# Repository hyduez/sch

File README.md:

# A Super Cool Hub

This project implements a budget and cool USB Hub thanks to the OTG USB feature that ESP32 S2/S3 brings on! On [BOM.md](https://github.com/hyduez/sch/blob/master/BOM.md) u can find each component with its own link to Aliexpress/Mouser. Due to expensive carriers fees and the niche market of Ecuador, it could be more than 20$ USD. The only firmware u are gonna need, is based on the brain of this PCB; if u want to do something when a state is detected, change the switch to flash the ESP32 and start coding. Anyways, this project aimed to be more; include OLED displays with tact buttons and commands to toggle data traveling, power on ports and show stats on the displays.

Here is the schematic:

You can see a lot of stuff that maybe u dont know where to start. But, as always, start where the power arises. Focus on the CH334F, it's the Mini Hub with 4 ports and another one for the host to manage, in this case, ESP32 S3 WROOM. It provides almost all the energy on the PCB, we are interesed on the 5V-A net label; it's gonna be merged with another line, 5V-B from SparkFun DEV-14050 (based on CH340G), this last one serve as auxiliar line, if u need more power available. Merged, they produce 5V-C, who is in charge of the USBs VBUS and ESP32 S3 WROOM power.

> [!IMPORTANT]
> Notice that this schematic is working with an ESP32 S3 WROOM, that's the reason why there's an AMS1117-3.3 that decrease the voltage from 5V to 3.3V; that's not neccesary with ESP32 S3 Devkit, since it brings its own regulator.

> [!TIP]
> Machine-readable fabrication outputs (Gerbers, drill, BOM CSV, pick and place,
> DRC/ERC) live in [`fabrication/`](fabrication), along with a
> [parts cross-check](fabrication/parts-check.md) against the BOM below. Before
> ordering, note that the PCB uses the bare CH334F QFN-24 and the bare
> ESP32-S3-WROOM-1 module, not the Adafruit breakout / devkit listed in
> [`BOM.md`](BOM.md).

The idea is that u'd add another coproccesor and create an useful artcraft hardware made by your hands, something to be proud. It's cool. You're not flexing something u bought on a minimarket, it's something u built and that's what matters.

## Index

- Inspiration & References
- Data Sheets & Components
- PCB Design
- Fabrication Files

## Inspiration & References
This is my first Hardware project strictly speaking. Instead of following guides, tutorials, projects pre-made; I decided to try it on my own. And here is how I got it: first, u need theory. It migh sounds cliche, but it's neccesary; u cannot start a journey without knowning how to start. Second, u must put into practice, and expand upon, what you DON'T KNOW; u might understand the fundamentals, but u cannot stop there, u've to be willing to try new and unfamiliar things. It seems too hard to make it? That doesn't matter, u're way ahead of it and u MUST be.

I started the last week without knowning even what a SMD, THT or SMT was, but that wasn't excuse to try in 2 days something REALLY cool, while managing a presencial event. I've already a sort of ideas that I wanted to do these 10 weeks, but I'm gonna stay to the most approachable and tuff thing to do. Between a lot of references, I've taken notice of this [resource](https://www.cnx-software.com/2024/11/04/usb-insight-hub-open-source-esp32-s2-based-for-testing-usb-devices/); and this image was an amazing motivation to design and build it.

## Data Sheets & Components

| Part | What it's for | Qty | Unit | Total | Vendor |
| --- | --- | --- | --- | --- | --- |
| [ESP32-S3 Devkit](https://es.aliexpress.com/item/1005008752956562.html?spm=a2g0o.productlist.main.2.56ea6619hSHeNG&algo_pvid=a7dce044-b750-4d39-8121-3cc3f7c3f446&algo_exp_id=a7dce044-b750-4d39-8121-3cc3f7c3f446-1&pdp_ext_f=%7B%22order%22%3A%224094%22%2C%22spu_best_type%22%3A%22price%22%2C%22eval%22%3A%221%22%2C%22fromPage%22%3A%22search%22%7D&pdp_npi=6%40dis%21USD%212.70%212.38%21%21%212.70%212.38%21%402141137e17917628397458067e0f4a%2112000048852579349%21sea%21EC%210%21ABX%211%210%21n_tag%3A-29910%3Bd%3A12ba086b%3Bm03_new_user%3A-29895&curPageLogUid=cDxGKN6VLdgP&utparam-url=scene%3Asearch%7Cquery_from%3A%7Cx_object_id%3A1005008752956562%7C_p_origin_prod%3A) | USB OTG and logic (more uses with the displays) | 1 | $2.38 | $2.38 | [Aliexpress](https://es.aliexpress.com/item/1005008752956562.html?spm=a2g0o.productlist.main.2.56ea6619hSHeNG&algo_pvid=a7dce044-b750-4d39-8121-3cc3f7c3f446&algo_exp_id=a7dce044-b750-4d39-8121-3cc3f7c3f446-1&pdp_ext_f=%7B%22order%22%3A%224094%22%2C%22spu_best_type%22%3A%22price%22%2C%22eval%22%3A%221%22%2C%22fromPage%22%3A%22search%22%7D&pdp_npi=6%40dis%21USD%212.70%212.38%21%21%212.70%212.38%21%402141137e17917628397458067e0f4a%2112000048852579349%21sea%21EC%210%21ABX%211%210%21n_tag%3A-29910%3Bd%3A12ba086b%3Bm03_new_user%3A-29895&curPageLogUid=cDxGKN6VLdgP&utparam-url=scene%3Asearch%7Cquery_from%3A%7Cx_object_id%3A1005008752956562%7C_p_origin_prod%3A) |
| [Adafruit CH334F 5999 Mini Hub USB 4 Ports](https://es.aliexpress.com/item/1005012286577528.html?spm=a2g0o.productlist.main.2.14c930fdv5VAiO&algo_pvid=f13fedb9-842e-44d2-a92c-3b4c332d380f&algo_exp_id=f13fedb9-842e-44d2-a92c-3b4c332d380f-1&pdp_ext_f=%7B%22order%22%3A%2260%22%2C%22spu_best_type%22%3A%22price%22%2C%22eval%22%3A%221%22%2C%22fromPage%22%3A%22search%22%7D&pdp_npi=6%40dis%21USD%214.55%214.55%21%21%2130.30%2130.30%21%400b08c0c217917628955407391e0cc5%2112000057968741991%21sea%21EC%210%21ABX%211%210%21n_tag%3A-29910%3Bd%3A12ba086b%3Bm03_new_user%3A-29895&curPageLogUid=nbacit8oiS5x&utparam-url=scene%3Asearch%7Cquery_from%3A%7Cx_object_id%3A1005012286577528%7C_p_origin_prod%3A) | USB Host and other ports, provides 5V to them | 1 | $4.55 | $4.55 | [Aliexpress](https://es.aliexpress.com/item/1005012286577528.html?spm=a2g0o.productlist.main.2.14c930fdv5VAiO&algo_pvid=f13fedb9-842e-44d2-a92c-3b4c332d380f&algo_exp_id=f13fedb9-842e-44d2-a92c-3b4c332d380f-1&pdp_ext_f=%7B%22order%22%3A%2260%22%2C%22spu_best_type%22%3A%22price%22%2C%22eval%22%3A%221%22%2C%22fromPage%22%3A%22search%22%7D&pdp_npi=6%40dis%21USD%214.55%214.55%21%21%2130.30%2130.30%21%400b08c0c217917628955407391e0cc5%2112000057968741991%21sea%21EC%210%21ABX%211%210%21n_tag%3A-29910%3Bd%3A12ba086b%3Bm03_new_user%3A-29895&curPageLogUid=nbacit8oiS5x&utparam-url=scene%3Asearch%7Cquery_from%3A%7Cx_object_id%3A1005012286577528%7C_p_origin_prod%3A) |
| [AMS1117-3.3](https://es.aliexpress.com/item/1005011789112180.html?spm=a2g0o.productlist.main.8.1d7940d1IDOKxH&algo_pvid=8ebd24b2-7b8b-4a43-9fbc-c8b7aa6dfdef&algo_exp_id=8ebd24b2-7b8b-4a43-9fbc-c8b7aa6dfdef-7&pdp_ext_f=%7B%22order%22%3A%22255%22%2C%22eval%22%3A%221%22%2C%22fromPage%22%3A%22search%22%7D&pdp_npi=6%40dis%21USD%214.50%212.07%21%21%2129.96%2113.78%21%402140cf5017917629953643864e0c9e%2112000056560577594%21sea%21EC%210%21ABX%211%210%21n_tag%3A-29910%3Bd%3A12ba086b%3Bm03_new_user%3A-29895&curPageLogUid=DT8fVeHC2Z0u&utparam-url=scene%3Asearch%7Cquery_from%3A%7Cx_object_id%3A1005011789112180%7C_p_origin_prod%3A) | Convert 5V to 3.3V (it shouldn't be neccesary because devkit editions use to bring their own regulators) | 1 | $2.07 | $2.07 | [Aliexpress](https://es.aliexpress.com/item/1005011789112180.html?spm=a2g0o.productlist.main.8.1d7940d1IDOKxH&algo_pvid=8ebd24b2-7b8b-4a43-9fbc-c8b7aa6dfdef&algo_exp_id=8ebd24b2-7b8b-4a43-9fbc-c8b7aa6dfdef-7&pdp_ext_f=%7B%22order%22%3A%22255%22%2C%22eval%22%3A%221%22%2C%22fromPage%22%3A%22search%22%7D&pdp_npi=6%40dis%21USD%214.50%212.07%21%21%2129.96%2113.78%21%402140cf5017917629953643864e0c9e%2112000056560577594%21sea%21EC%210%21ABX%211%210%21n_tag%3A-29910%3Bd%3A12ba086b%3Bm03_new_user%3A-29895&curPageLogUid=DT8fVeHC2Z0u&utparam-url=scene%3Asearch%7Cquery_from%3A%7Cx_object_id%3A1005011789112180%7C_p_origin_prod%3A) |
| [Resistors (10k)](https://es.aliexpress.com/item/1005012752130462.html?spm=a2g0o.productlist.main.17.1c8b2c1aXSGf5r&algo_pvid=4282fd54-1a4b-4560-b2d5-20b68522da93&algo_exp_id=4282fd54-1a4b-4560-b2d5-20b68522da93-16&pdp_ext_f=%7B%22order%22%3A%22129%22%2C%22eval%22%3A%221%22%2C%22fromPage%22%3A%22search%22%7D&pdp_npi=6%40dis%21USD%210.85%210.78%21%21%210.85%210.78%21%402140cf5017917630669585191e0c9e%2112000059788474300%21sea%21EC%210%21ABX%211%210%21n_tag%3A-29910%3Bd%3A12ba086b%3Bm03_new_user%3A-29895&curPageLogUid=QCaruf2H9BXq&utparam-url=scene%3Asearch%7Cquery_from%3A%7Cx_object_id%3A1005012752130462%7C_p_origin_prod%3A) | Electronics | 1 | $0.78 | $0.78 | [Aliexpress](https://es.aliexpress.com/item/1005012752130462.html?spm=a2g0o.productlist.main.17.1c8b2c1aXSGf5r&algo_pvid=4282fd54-1a4b-4560-b2d5-20b68522da93&algo_exp_id=4282fd54-1a4b-4560-b2d5-20b68522da93-16&pdp_ext_f=%7B%22order%22%3A%22129%22%2C%22eval%22%3A%221%22%2C%22fromPage%22%3A%22search%22%7D&pdp_npi=6%40dis%21USD%210.85%210.78%21%21%210.85%210.78%21%402140cf5017917630669585191e0c9e%2112000059788474300%21sea%21EC%210%21ABX%211%210%21n_tag%3A-29910%3Bd%3A12ba086b%3Bm03_new_user%3A-29895&curPageLogUid=QCaruf2H9BXq&utparam-url=scene%3Asearch%7Cquery_from%3A%7Cx_object_id%3A1005012752130462%7C_p_origin_prod%3A) |
| [Capacitor (1uf)](https://es.aliexpress.com/item/1005003382101471.html?spm=a2g0o.productlist.main.3.617723cbL9pqqJ&algo_pvid=187cdbcc-065d-4fdd-bee1-079ebf859f36&algo_exp_id=187cdbcc-065d-4fdd-bee1-079ebf859f36-2&pdp_ext_f=%7B%22order%22%3A%22134%22%2C%22eval%22%3A%221%22%2C%22fromPage%22%3A%22search%22%7D&pdp_npi=6%40dis%21USD%210.83%210.82%21%21%215.50%215.44%21%40210159d417917631330304275e0d23%2112000025520782166%21sea%21EC%210%21ABX%211%210%21n_tag%3A-29910%3Bd%3A12ba086b%3Bm03_new_user%3A-29895&curPageLogUid=pA2ZzqVH0y7b&utparam-url=scene%3Asearch%7Cquery_from%3A%7Cx_object_id%3A1005003382101471%7C_p_origin_prod%3A) | Electronics | 1 | $0.82 | $0.82 | [Aliexpress](https://es.aliexpress.com/item/1005003382101471.html?spm=a2g0o.productlist.main.3.617723cbL9pqqJ&algo_pvid=187cdbcc-065d-4fdd-bee1-079ebf859f36&algo_exp_id=187cdbcc-065d-4fdd-bee1-079ebf859f36-2&pdp_ext_f=%7B%22order%22%3A%22134%22%2C%22eval%22%3A%221%22%2C%22fromPage%22%3A%22search%22%7D&pdp_npi=6%40dis%21USD%210.83%210.82%21%21%215.50%215.44%21%40210159d417917631330304275e0d23%2112000025520782166%21sea%21EC%210%21ABX%211%210%21n_tag%3A-29910%3Bd%3A12ba086b%3Bm03_new_user%3A-29895&curPageLogUid=pA2ZzqVH0y7b&utparam-url=scene%3Asearch%7Cquery_from%3A%7Cx_object_id%3A1005003382101471%7C_p_origin_prod%3A) |
| [Capacitor (10uf)](https://es.aliexpress.com/item/1005004338780216.html?spm=a2g0o.productlist.main.3.322223e9fjoMPA&algo_pvid=524ed1cf-a28f-4dc1-a7a2-89a9e72d1312&algo_exp_id=524ed1cf-a28f-4dc1-a7a2-89a9e72d1312-2&pdp_ext_f=%7B%22order%22%3A%22237%22%2C%22eval%22%3A%221%22%2C%22fromPage%22%3A%22search%22%7D&pdp_npi=6%40dis%21USD%210.97%210.68%21%21%210.97%210.68%21%40212e37e817917631883788663e0c8f%2112000028814428355%21sea%21EC%210%21ABX%211%210%21n_tag%3A-29910%3Bd%3A12ba086b%3Bm03_new_user%3A-29895&curPageLogUid=EJPw3F4KWMpT&utparam-url=scene%3Asearch%7Cquery_from%3A%7Cx_object_id%3A1005004338780216%7C_p_origin_prod%3A) | Electronics | 1 | $0.68 | $0.68 | [Aliexpress](https://es.aliexpress.com/item/1005004338780216.html?spm=a2g0o.productlist.main.3.322223e9fjoMPA&algo_pvid=524ed1cf-a28f-4dc1-a7a2-89a9e72d1312&algo_exp_id=524ed1cf-a28f-4dc1-a7a2-89a9e72d1312-2&pdp_ext_f=%7B%22order%22%3A%22237%22%2C%22eval%22%3A%221%22%2C%22fromPage%22%3A%22search%22%7D&pdp_npi=6%40dis%21USD%210.97%210.68%21%21%210.97%210.68%21%40212e37e817917631883788663e0c8f%2112000028814428355%21sea%21EC%210%21ABX%211%210%21n_tag%3A-29910%3Bd%3A12ba086b%3Bm03_new_user%3A-29895&curPageLogUid=EJPw3F4KWMpT&utparam-url=scene%3Asearch%7Cquery_from%3A%7Cx_object_id%3A1005004338780216%7C_p_origin_prod%3A) |
| [Led Diode](https://es.aliexpress.com/item/1005004543292837.html?spm=a2g0o.productlist.main.1.21d0e14dVRjCgZ&algo_pvid=ccc14f9d-805c-4f90-938d-073c46266c18&algo_exp_id=ccc14f9d-805c-4f90-938d-073c46266c18-0&pdp_ext_f=%7B%22order%22%3A%226583%22%2C%22spu_best_type%22%3A%22price%22%2C%22eval%22%3A%221%22%2C%22fromPage%22%3A%22search%22%7D&pdp_npi=6%40dis%21USD%212.07%211.97%21%21%2113.76%2113.07%21%40212e37e817917633191452847e0c8f%2112000029546625285%21sea%21EC%210%21ABX%211%210%21n_tag%3A-29910%3Bd%3A12ba086b%3Bm03_new_user%3A-29895&curPageLogUid=2ixU2qk83hql&utparam-url=scene%3Asearch%7Cquery_from%3A%7Cx_object_id%3A1005004543292837%7C_p_origin_prod%3A) | Misc | 1 | $1.97 | $1.97 | [Aliexpress](https://es.aliexpress.com/item/1005004543292837.html?spm=a2g0o.productlist.main.1.21d0e14dVRjCgZ&algo_pvid=ccc14f9d-805c-4f90-938d-073c46266c18&algo_exp_id=ccc14f9d-805c-4f90-938d-073c46266c18-0&pdp_ext_f=%7B%22order%22%3A%226583%22%2C%22spu_best_type%22%3A%22price%22%2C%22eval%22%3A%221%22%2C%22fromPage%22%3A%22search%22%7D&pdp_npi=6%40dis%21USD%212.07%211.97%21%21%2113.76%2113.07%21%40212e37e817917633191452847e0c8f%2112000029546625285%21sea%21EC%210%21ABX%211%210%21n_tag%3A-29910%3Bd%3A12ba086b%3Bm03_new_user%3A-29895&curPageLogUid=2ixU2qk83hql&utparam-url=scene%3Asearch%7Cquery_from%3A%7Cx_object_id%3A1005004543292837%7C_p_origin_prod%3A) |
| [CH340G USB-C Female 3.3V & 5V](https://es.aliexpress.com/item/1005009973324450.html?spm=a2g0o.productlist.main.8.2ea226deptqf7i&algo_pvid=015248a2-db7a-48a4-b338-fae4d3fea4a1&algo_exp_id=015248a2-db7a-48a4-b338-fae4d3fea4a1-7&pdp_ext_f=%7B%22order%22%3A%22165%22%2C%22spu_best_type%22%3A%22price%22%2C%22eval%22%3A%221%22%2C%22fromPage%22%3A%22search%22%7D&pdp_npi=6%40dis%21USD%213.86%211.85%21%21%2125.72%2112.35%21%40210159a517917633550661626e0cf8%2112000050730857128%21sea%21EC%210%21ABX%211%210%21n_tag%3A-29910%3Bd%3A12ba086b%3Bm03_new_user%3A-29895&curPageLogUid=ahEIKOvfgL6V&utparam-url=scene%3Asearch%7Cquery_from%3A%7Cx_object_id%3A1005009973324450%7C_p_origin_prod%3A) | Auxiliar energy source | 1 | $1.85 | $1.85 | [Aliexpress](https://es.aliexpress.com/item/1005009973324450.html?spm=a2g0o.productlist.main.8.2ea226deptqf7i&algo_pvid=015248a2-db7a-48a4-b338-fae4d3fea4a1&algo_exp_id=015248a2-db7a-48a4-b338-fae4d3fea4a1-7&pdp_ext_f=%7B%22order%22%3A%22165%22%2C%22spu_best_type%22%3A%22price%22%2C%22eval%22%3A%221%22%2C%22fromPage%22%3A%22search%22%7D&pdp_npi=6%40dis%21USD%213.86%211.85%21%21%2125.72%2112.35%21%40210159a517917633550661626e0cf8%2112000050730857128%21sea%21EC%210%21ABX%211%210%21n_tag%3A-29910%3Bd%3A12ba086b%3Bm03_new_user%3A-29895&curPageLogUid=ahEIKOvfgL6V&utparam-url=scene%3Asearch%7Cquery_from%3A%7Cx_object_id%3A1005009973324450%7C_p_origin_prod%3A) |
| [1N5819 Diodes Schottky](https://es.aliexpress.com/item/32854878050.html?spm=a2g0o.productlist.main.1.711f4f10e92eCH&algo_pvid=0c70d40a-1a3c-4e26-88f5-180aee8b8167&algo_exp_id=0c70d40a-1a3c-4e26-88f5-180aee8b8167-0&pdp_ext_f=%7B%22order%22%3A%22114%22%2C%22eval%22%3A%221%22%2C%22fromPage%22%3A%22search%22%7D&pdp_npi=6%40dis%21USD%211.13%211.07%21%21%211.13%211.07%21%40210159a517917634506883193e0cf8%2165279246473%21sea%21EC%210%21ABX%211%210%21n_tag%3A-29910%3Bd%3A12ba086b%3Bm03_new_user%3A-29895&curPageLogUid=gfQc0vqEISYV&utparam-url=scene%3Asearch%7Cquery_from%3A%7Cx_object_id%3A32854878050%7C_p_origin_prod%3A) | Power muxer between CH334F and CH340G 5V | 1 | $1.07 | $1.07 | [Aliexpress](https://es.aliexpress.com/item/32854878050.html?spm=a2g0o.productlist.main.1.711f4f10e92eCH&algo_pvid=0c70d40a-1a3c-4e26-88f5-180aee8b8167&algo_exp_id=0c70d40a-1a3c-4e26-88f5-180aee8b8167-0&pdp_ext_f=%7B%22order%22%3A%22114%22%2C%22eval%22%3A%221%22%2C%22fromPage%22%3A%22search%22%7D&pdp_npi=6%40dis%21USD%211.13%211.07%21%21%211.13%211.07%21%40210159a517917634506883193e0cf8%2165279246473%21sea%21EC%210%21ABX%211%210%21n_tag%3A-29910%3Bd%3A12ba086b%3Bm03_new_user%3A-29895&curPageLogUid=gfQc0vqEISYV&utparam-url=scene%3Asearch%7Cquery_from%3A%7Cx_object_id%3A32854878050%7C_p_origin_prod%3A) |
| [Capacitor (100nf) (KGM05AR51A104KN)](https://www.mouser.ec/en/ProductDetail/KYOCERA-AVX/KGM05AR51A104KN?qs=Jm2GQyTW%2Fbi5bvYnwKdugg%3D%3D) | Electronics | 2 | $0.32 | $0.64 | [Mouser](https://www.mouser.ec/en/ProductDetail/KYOCERA-AVX/KGM05AR51A104KN?qs=Jm2GQyTW%2Fbi5bvYnwKdugg%3D%3D) |
| [Tactil Button 4.3](https://es.aliexpress.com/item/1005005549119220.html?spm=a2g0o.productlist.main.1.5ccd1020kha8Bg&algo_pvid=2b03a42a-50ce-4adc-afa1-d793b0f735b8&algo_exp_id=2b03a42a-50ce-4adc-afa1-d793b0f735b8-0&pdp_ext_f=%7B%22order%22%3A%22513%22%2C%22eval%22%3A%221%22%2C%22fromPage%22%3A%22search%22%7D&pdp_npi=6%40dis%21USD%210.88%210.79%21%21%210.88%210.79%21%402102f7bd17917638156187256e0fd4%2112000033497740421%21sea%21EC%210%21ABX%211%210%21n_tag%3A-29910%3Bd%3A12ba086b%3Bm03_new_user%3A-29895&curPageLogUid=2k5vIwR9Gi5m&utparam-url=scene%3Asearch%7Cquery_from%3A%7Cx_object_id%3A1005005549119220%7C_p_origin_prod%3A) | Switch for the ESP32 | 1 | $0.79 | $0.79 | [Aliexpress](https://es.aliexpress.com/item/1005005549119220.html?spm=a2g0o.productlist.main.1.5ccd1020kha8Bg&algo_pvid=2b03a42a-50ce-4adc-afa1-d793b0f735b8&algo_exp_id=2b03a42a-50ce-4adc-afa1-d793b0f735b8-0&pdp_ext_f=%7B%22order%22%3A%22513%22%2C%22eval%22%3A%221%22%2C%22fromPage%22%3A%22search%22%7D&pdp_npi=6%40dis%21USD%210.88%210.79%21%21%210.88%210.79%21%402102f7bd17917638156187256e0fd4%2112000033497740421%21sea%21EC%210%21ABX%211%210%21n_tag%3A-29910%3Bd%3A12ba086b%3Bm03_new_user%3A-29895&curPageLogUid=2k5vIwR9Gi5m&utparam-url=scene%3Asearch%7Cquery_from%3A%7Cx_object_id%3A1005005549119220%7C_p_origin_prod%3A) |
| [Hook-up Wires](https://es.aliexpress.com/item/1005008563576114.html?spm=a2g0o.productlist.main.1.664d4b4b7wJWWy&algo_pvid=39365065-7a89-4fde-bb6e-e4ea4540c1a9&algo_exp_id=39365065-7a89-4fde-bb6e-e4ea4540c1a9-0&pdp_ext_f=%7B%22order%22%3A%2231223%22%2C%22spu_best_type%22%3A%22price%22%2C%22eval%22%3A%221%22%2C%22fromPage%22%3A%22search%22%7D&pdp_npi=6%40dis%21USD%213.71%213.71%21%21%2124.70%2124.70%21%402101528c17917638773475139e0fd4%2112000045733462558%21sea%21EC%210%21ABX%211%210%21n_tag%3A-29910%3Bd%3A12ba086b%3Bm03_new_user%3A-29895&curPageLogUid=A20gy6g0xdJd&utparam-url=scene%3Asearch%7Cquery_from%3A%7Cx_object_id%3A1005008563576114%7C_p_origin_prod%3A) | To connect everything | 1 | $3.71 | $3.71 | [Aliexpress](https://es.aliexpress.com/item/1005008563576114.html?spm=a2g0o.productlist.main.1.664d4b4b7wJWWy&algo_pvid=39365065-7a89-4fde-bb6e-e4ea4540c1a9&algo_exp_id=39365065-7a89-4fde-bb6e-e4ea4540c1a9-0&pdp_ext_f=%7B%22order%22%3A%2231223%22%2C%22spu_best_type%22%3A%22price%22%2C%22eval%22%3A%221%22%2C%22fromPage%22%3A%22search%22%7D&pdp_npi=6%40dis%21USD%213.71%213.71%21%21%2124.70%2124.70%21%402101528c17917638773475139e0fd4%2112000045733462558%21sea%21EC%210%21ABX%211%210%21n_tag%3A-29910%3Bd%3A12ba086b%3Bm03_new_user%3A-29895&curPageLogUid=A20gy6g0xdJd&utparam-url=scene%3Asearch%7Cquery_from%3A%7Cx_object_id%3A1005008563576114%7C_p_origin_prod%3A) |
| [USB-A Dip Connector 2.54mm](https://es.aliexpress.com/item/1005010686097914.html?spm=a2g0o.productlist.main.32.627d120a9faCQe&algo_pvid=ec453c04-842f-4509-b627-83b8270896d8&algo_exp_id=ec453c04-842f-4509-b627-83b8270896d8-31&pdp_ext_f=%7B%22order%22%3A%2254%22%2C%22eval%22%3A%221%22%2C%22fromPage%22%3A%22search%22%7D&pdp_npi=6%40dis%21USD%212.89%212.31%21%21%2119.24%2115.39%21%402101364a17917639668701473e0e3c%2112000053188161885%21sea%21EC%210%21ABX%211%210%21n_tag%3A-29910%3Bd%3A12ba086b%3Bm03_new_user%3A-29895&curPageLogUid=wjXYxHCDXvPi&utparam-url=scene%3Asearch%7Cquery_from%3A%7Cx_object_id%3A1005010686097914%7C_p_origin_prod%3A) | That's kinda obvious. | 1 | $2.31 | $2.31 | [Aliexpress](https://es.aliexpress.com/item/1005010686097914.html?spm=a2g0o.productlist.main.32.627d120a9faCQe&algo_pvid=ec453c04-842f-4509-b627-83b8270896d8&algo_exp_id=ec453c04-842f-4509-b627-83b8270896d8-31&pdp_ext_f=%7B%22order%22%3A%2254%22%2C%22eval%22%3A%221%22%2C%22fromPage%22%3A%22search%22%7D&pdp_npi=6%40dis%21USD%212.89%212.31%21%21%2119.24%2115.39%21%402101364a17917639668701473e0e3c%2112000053188161885%21sea%21EC%210%21ABX%211%210%21n_tag%3A-29910%3Bd%3A12ba086b%3Bm03_new_user%3A-29895&curPageLogUid=wjXYxHCDXvPi&utparam-url=scene%3Asearch%7Cquery_from%3A%7Cx_object_id%3A1005010686097914%7C_p_origin_prod%3A) |
| **Parts subtotal** | — | — | — | **$23.62** | — |
| **Tax & shipping** | — | — | — | **$20.00** | — |
| **Total** | — | — | — | **$43.62** | — |

And also the following data sheets:

- [CH334F](https://cdn-learn.adafruit.com/assets/assets/000/131/435/original/CH334DS1.PDF)
- [ESP32 S3 Schematic Checklist](https://docs.espressif.com/projects/esp-hardware-design-guidelines/en/latest/esp32s3/schematic-checklist.html)

and even more, but they are missed.

## PCB Design

I have to be honest, it was kinda messy, but it was part of my learning and I'm okay with it :p I designed it more than three times in a row just to make it look prettier and logic, not only wiring for the sake of doing it. I learnt a lot of things and I'm feeling more conformtable using KiCAD (schematic, pcb desing) and I hope I'm gonna do the same with the CAD week! I'm gonna take a look to the guide of this week, I hope to see a tutorial on OpenShape.

I also hope to build this project on week 6 and bring it to live, wait some updates on it anyways on the next days/weeks/months. I'm so excited to keep learning and participating on Half Life!! :)

## Fabrication Files

Everything a fab house or an assembly service needs is generated from the KiCad
project and checked in under [`fabrication/`](fabrication):

| What | File |
| --- | --- |
| Gerbers + drill (upload this to the PCB house) | [`fabrication/sch-gerbers.zip`](fabrication/sch-gerbers.zip) |
| Plain Gerbers (X2, 9 layers) | [`fabrication/gerbers/`](fabrication/gerbers) |
| Drill files (Excellon, mm, PTH/NPTH split) + maps | [`fabrication/drill/`](fabrication/drill) |
| Bill of materials (CSV, grouped by value) | [`fabrication/bom/sch-bom.csv`](fabrication/bom/sch-bom.csv) |
| Pick and place / centroid (CSV, mm) | [`fabrication/pick-and-place/`](fabrication/pick-and-place) |
| DRC + ERC + board stats | [`fabrication/reports/`](fabrication/reports) |
| Schematic & PCB PDFs | [`fabrication/plots/`](fabrication/plots) |

The board is 2 layers, 1.6 mm, 81.1 x 75.6 mm, with 22 footprints (18 SMD, 4
THT), all placed on the front side, so it can be assembled with a single-side
stencil. [`BOM.md`](BOM.md) is the shopping list from Half Life with vendor
links; the CSV in `fabrication/bom/` is the machine-readable version generated
from the schematic, so the two are worth cross-checking before ordering.

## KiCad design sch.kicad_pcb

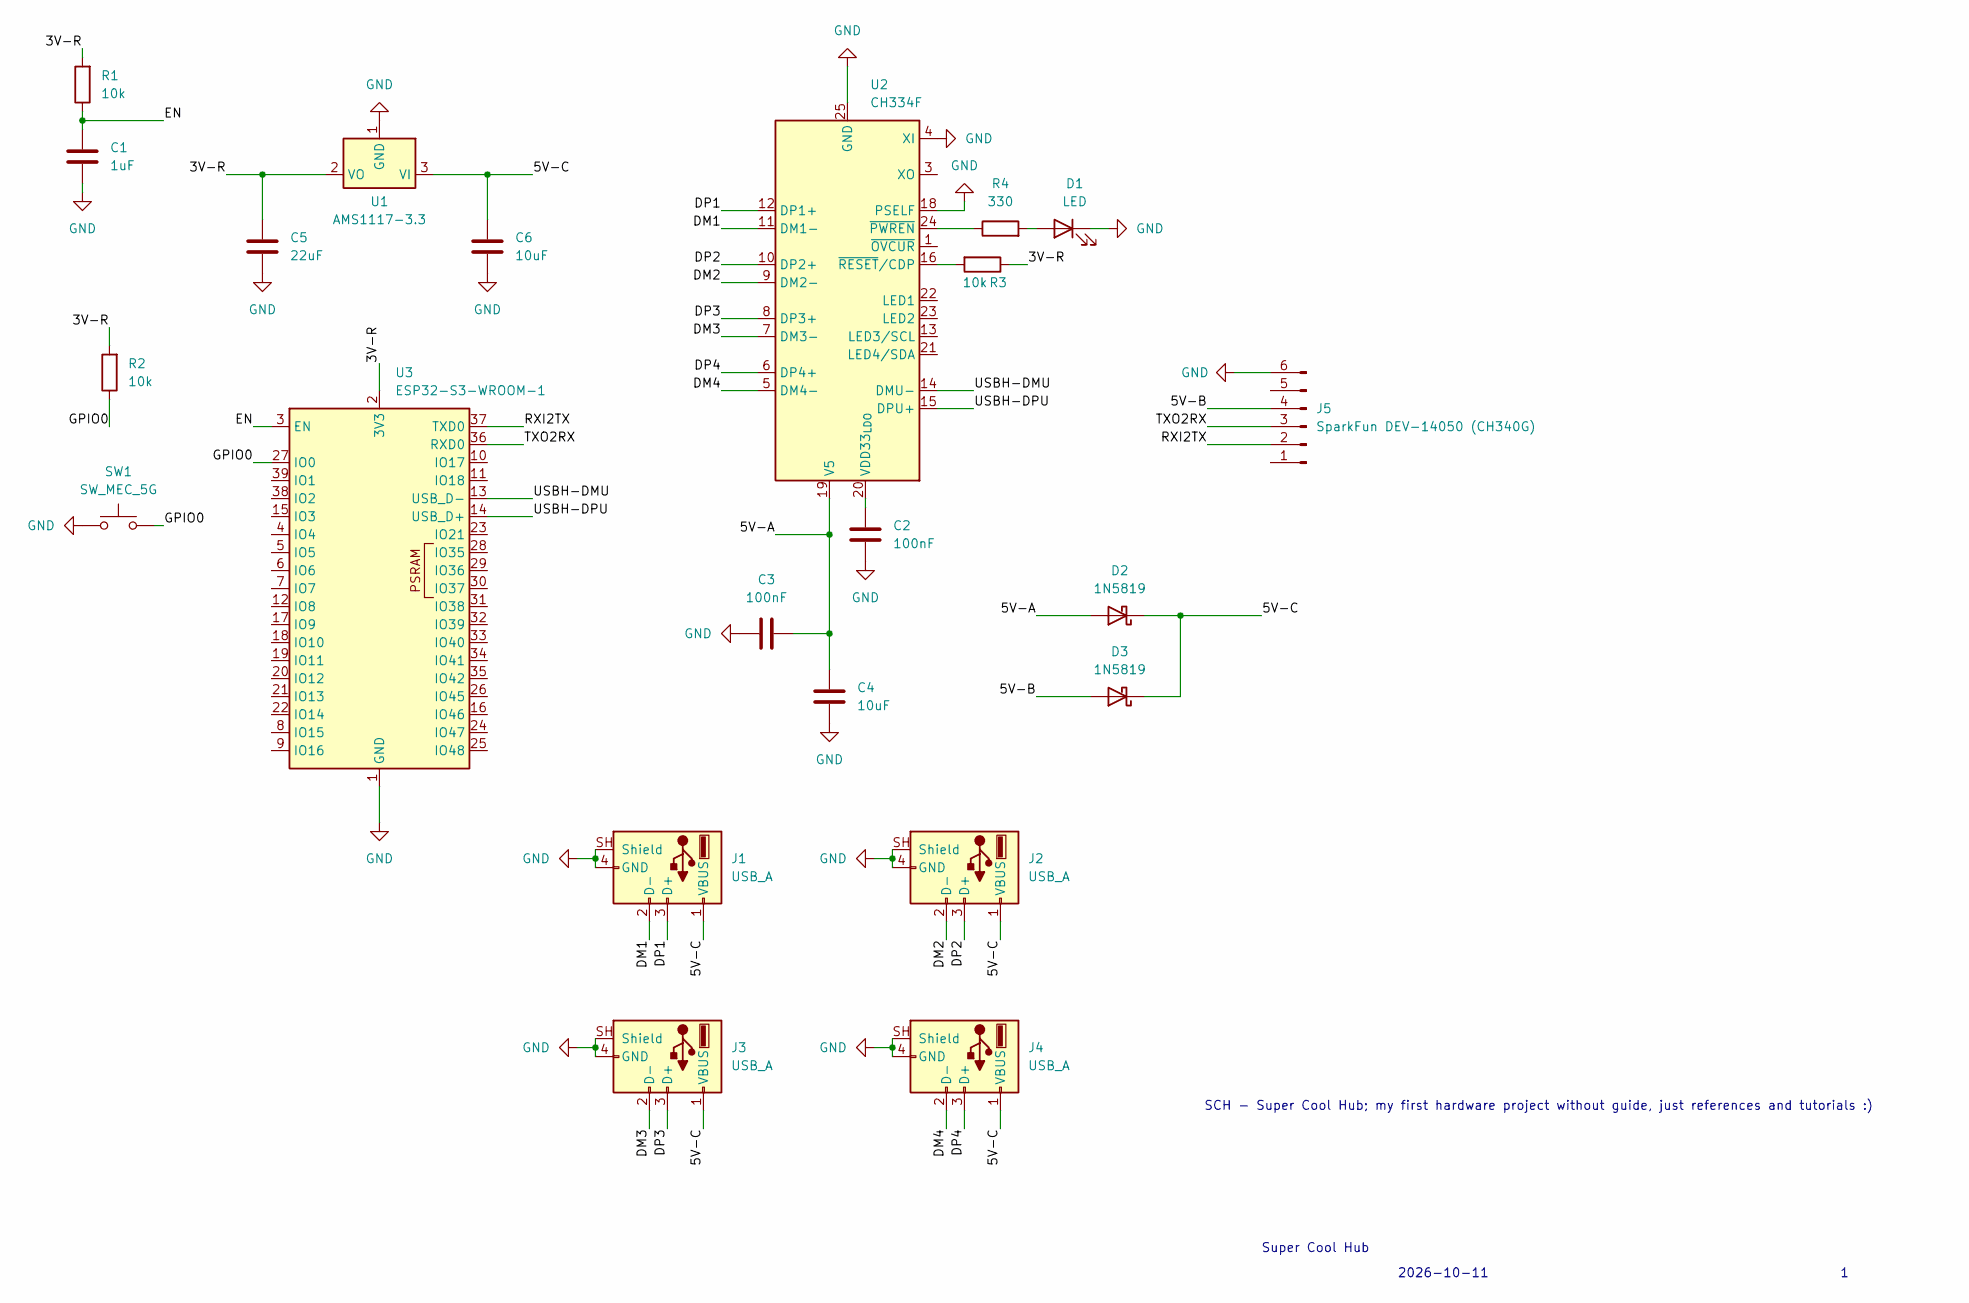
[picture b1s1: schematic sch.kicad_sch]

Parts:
C1: 1uF; C_0805_2012Metric
C2, C3: 100nF; C_0805_2012Metric
C4, C6: 10uF; C_0805_2012Metric
C5: 22uF; C_0805_2012Metric
D1: LED; LED_0805_2012Metric
D2, D3: 1N5819; D_DO-41_SOD81_P10.16mm_Horizontal
J1, J2, J3, J4: USB_A; USB_A_Connfly_DS1098_Horizontal
J5: SparkFun DEV-14050 (CH340G); PinHeader_1x06_P2.54mm_Vertical
R1, R2, R3: 10k; R_0805_2012Metric
R4: 330; R_0805_2012Metric
SW1: SW_MEC_5G; SW_PUSH_6mm
U1: AMS1117-3.3; SOT-223-3_TabPin2
U2: CH334F; QFN-24-1EP_4x4mm_P0.5mm_EP2.7x2.7mm
U3: ESP32-S3-WROOM-1

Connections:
/3V-R: C5.1, R1.2, R2.2, R3.1, U1.2 (VO), U3.2 (3V3)
/5V-A: C3.2, C4.2, D2.2 (A), U2.19 (V5)
/5V-B: D3.2 (A), J5.4
/5V-C: C6.1, D2.1 (K), D3.1 (K), J1.1 (VBUS), J2.1 (VBUS), J3.1 (VBUS), J4.1 (VBUS), U1.3 (VI)
/DM1: J1.2 (D-), U2.11 (DM1-)
/DM2: J2.2 (D-), U2.9 (DM2-)
/DM3: J3.2 (D-), U2.7 (DM3-)
/DM4: J4.2 (D-), U2.5 (DM4-)
/DP1: J1.3 (D+), U2.12 (DP1+)
/DP2: J2.3 (D+), U2.10 (DP2+)
/DP3: J3.3 (D+), U2.8 (DP3+)
/DP4: J4.3 (D+), U2.6 (DP4+)
/EN: C1.1, R1.1, U3.3 (EN)
/GPIO0: R2.1, SW1.3 (B), SW1.4 (B), U3.27 (IO0)
/RXI2TX: J5.2, U3.37 (TXD0)
/TXO2RX: J5.3, U3.36 (RXD0)
/USBH-DMU: U2.14 (DMU-), U3.13 (USB_D-)
/USBH-DPU: U2.15 (DPU+), U3.14 (USB_D+)
GND: C1.2, C2.2, C3.1, C4.1, C5.2, C6.2, D1.1 (K), J1.4 (GND), J1.SH (Shield), J2.4 (GND), J2.SH (Shield), J3.4 (GND), J3.SH (Shield), J4.4 (GND), J4.SH (Shield), J5.6, SW1.1 (A), SW1.2 (A), U1.1 (GND), U2.4 (XI), U2.18 (PSELF), U2.25 (GND), U3.1 (GND), U3.40 (GND), U3.41 (GND)
unnamed: D1.2 (A), R4.2
unnamed: C2.1, U2.20 (VDD33_{LDO})
unnamed: R4.1, U2.24 (~PWREN)
unnamed: R3.2, U2.16 (~RESET/CDP)

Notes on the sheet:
2026-10-11
SCH - Super Cool Hub; my first hardware project without guide, just references and tutorials :)
Super Cool Hub

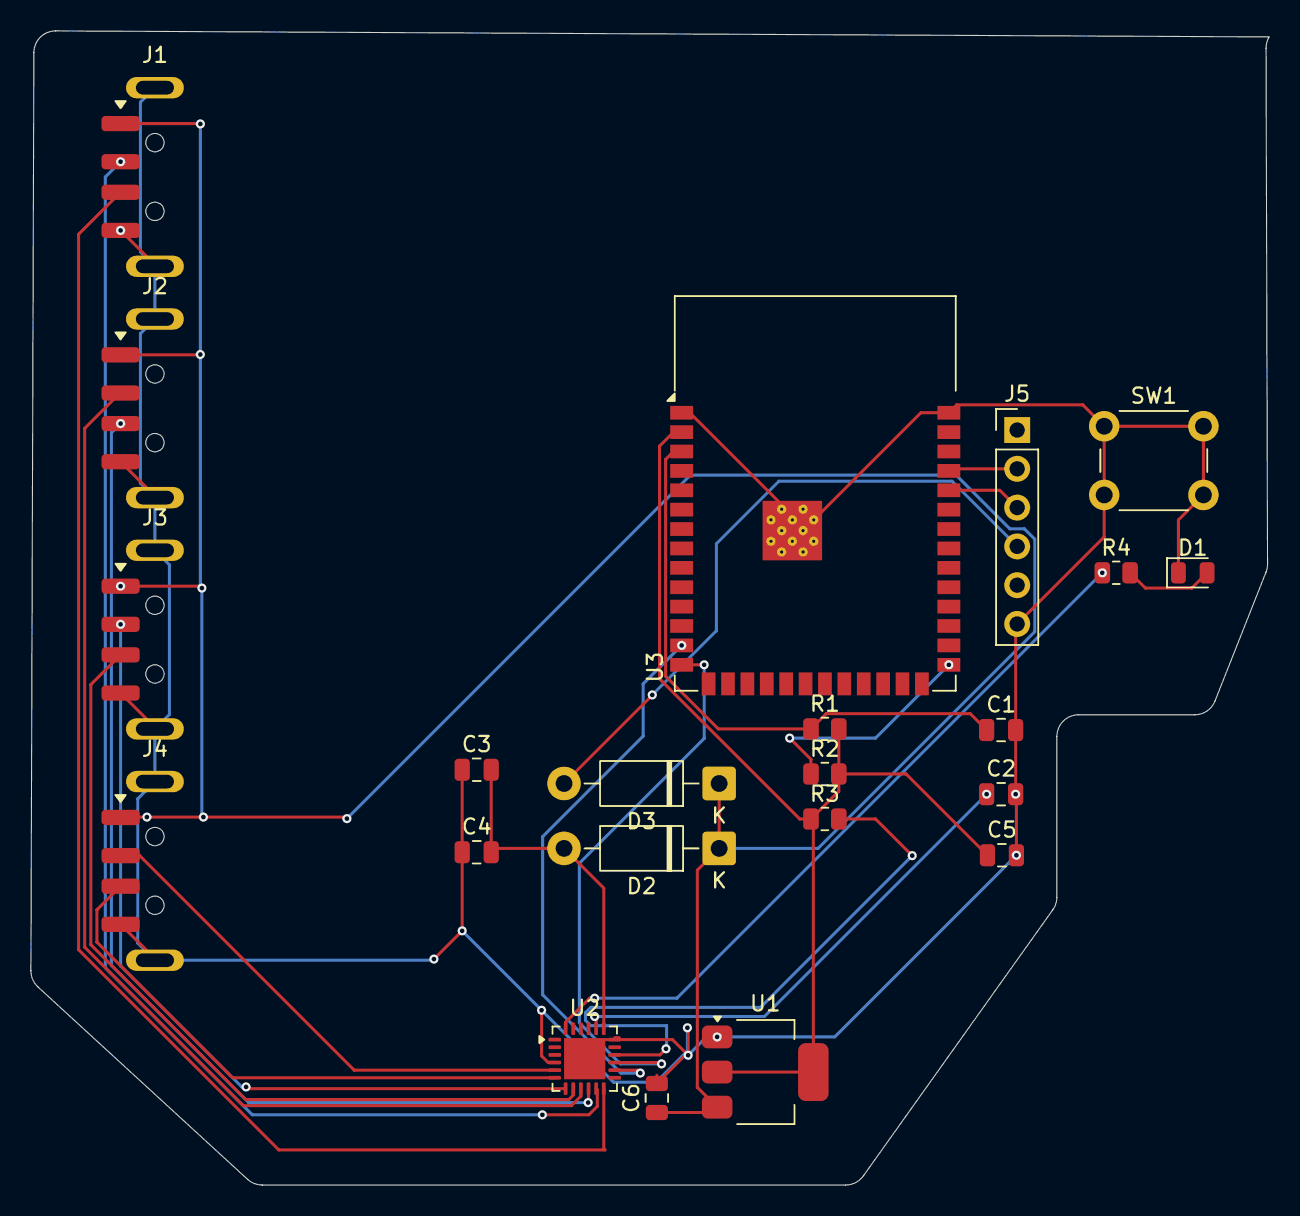
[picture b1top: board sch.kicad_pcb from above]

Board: 2 copper layers, 81.1 x 75.6 mm, 22 parts (0 on the bottom side), 23 nets.

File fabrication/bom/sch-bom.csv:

"Refs","Value","Footprint","Qty","DNP","Description"
"C1","1uF","Capacitor_SMD:C_0805_2012Metric","1","","Unpolarized capacitor"
"C2,C3","100nF","Capacitor_SMD:C_0805_2012Metric","2","","Unpolarized capacitor"
"C4,C6","10uF","Capacitor_SMD:C_0805_2012Metric","2","","Unpolarized capacitor"
"C5","22uF","Capacitor_SMD:C_0805_2012Metric","1","","Unpolarized capacitor"
"D1","LED","LED_SMD:LED_0805_2012Metric","1","","Light emitting diode"
"D2,D3","1N5819","Diode_THT:D_DO-41_SOD81_P10.16mm_Horizontal","2","","40V 1A Schottky Barrier Rectifier Diode, DO-41"
"J1-J4","USB_A","Connector_USB:USB_A_Connfly_DS1098_Horizontal","4","","USB Type A connector"
"J5","SparkFun DEV-14050 (CH340G)","Connector_PinHeader_2.54mm:PinHeader_1x06_P2.54mm_Vertical","1","","Generic connector, single row, 01x06, script generated"
"R1-R3","10k","Resistor_SMD:R_0805_2012Metric","3","","Resistor"
"R4","330","Resistor_SMD:R_0805_2012Metric","1","","Resistor"
"SW1","SW_MEC_5G","Button_Switch_THT:SW_PUSH_6mm","1","","MEC 5G single pole normally-open tactile switch"
"U1","AMS1117-3.3","Package_TO_SOT_SMD:SOT-223-3_TabPin2","1","","1A Low Dropout regulator, positive, 3.3V fixed output, SOT-223"
"U2","CH334F","Package_DFN_QFN:QFN-24-1EP_4x4mm_P0.5mm_EP2.7x2.7mm","1","","USB HUB controller, QFN-24"
"U3","ESP32-S3-WROOM-1","RF_Module:ESP32-S3-WROOM-1","1","","RF Module, ESP32-S3 SoC, Wi-Fi 802.11b/g/n, Bluetooth, BLE, 32-bit, 3.3V, onboard antenna, SMD"
